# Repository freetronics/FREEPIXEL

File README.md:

Freetronics FreePixel Addressable RGB LED Module
=================================================
Copyright 2016 Freetronics Pty Ltd  
Freetronics site:  www.freetronics.com  
Freetronics email: info@freetronics.com  

This is an LED with a brain! Includes a bright RGB LED with a built-in
WS2812B constant-current, addressable, multi-channel LED driver. This
smart module can be daisy-chained, so you can connect a number of these
together in a string and drive each of the module colours individually
from your microcontroller.

Compatible with various Arduino libraries for the WS2812B, including
the FastLED library and the NeoPixel library.

Features:

 * Requires just 1 data connections.
 * Input and output headers on opposite sides of the board for easy
   daisy-chaining.

More information is available at:

  http://www.freetronics.com.au/freepixel

INSTALLATION
------------
The design is saved as an EAGLE project. EAGLE PCB design software is
available from www.cadsoftusa.com free for non-commercial use. To use
this project download it and place the directory containing these files
into the "eagle" directory on your computer.

DISTRIBUTION
------------
The specific terms of distribution of this project are governed by the
license referenced below.

LICENSE
-------
Licensed under the TAPR Open Hardware License (www.tapr.org/OHL).
The "license" folder within this repository also contains a copy of
this license in plain text format.

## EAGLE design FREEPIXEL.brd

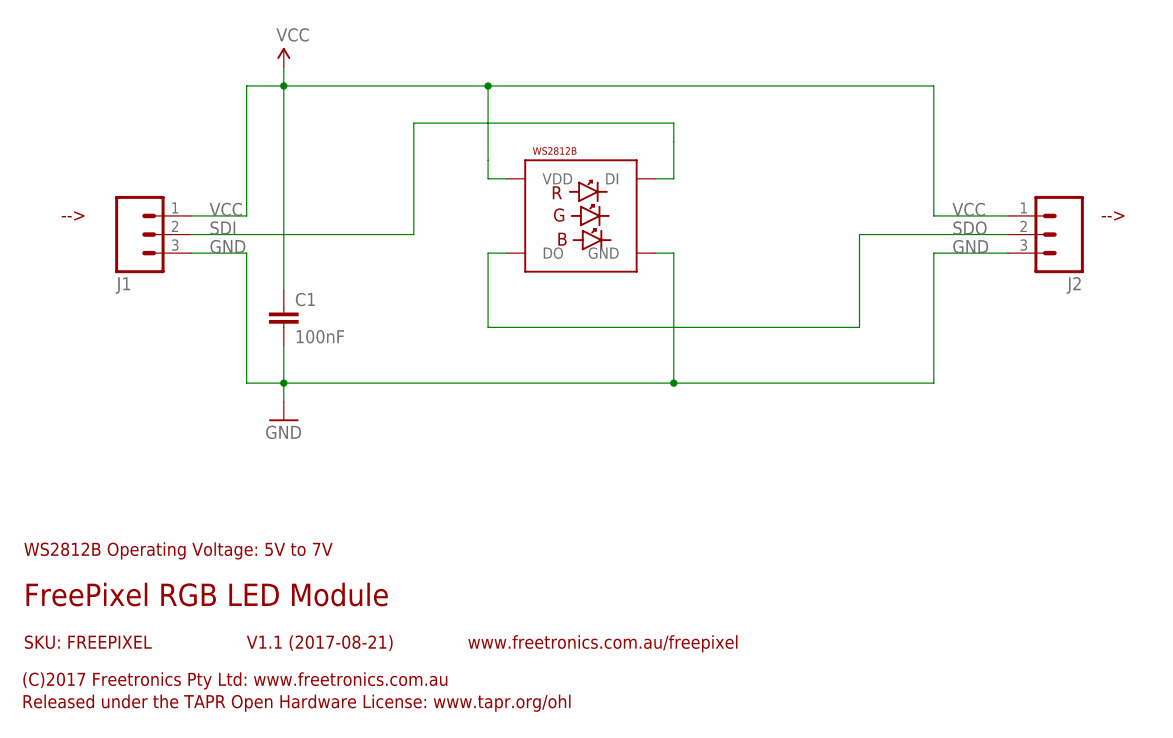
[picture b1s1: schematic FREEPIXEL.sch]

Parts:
C1: 100nF; 0603
J1, J2: M03PTH; 1X03
LED1: WS2812B5050; WS2812B

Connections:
GND: C1.2, J1.3, J2.3, LED1.3-GND (GND)
SDI: J1.2, LED1.4-DIN (DI)
SDO: J2.2, LED1.2-DOUT (DO)
VCC: C1.1, J1.1, J2.1, LED1.1-VDD (VDD)

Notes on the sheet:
FreePixel RGB LED Module
V1.1 (2017-08-21)
SKU: FREEPIXEL
(C)2017 Freetronics Pty Ltd: www.freetronics.com.au
Released under the TAPR Open Hardware License: www.tapr.org/ohl
www.freetronics.com.au/freepixel
WS2812B Operating Voltage: 5V to 7V
-->

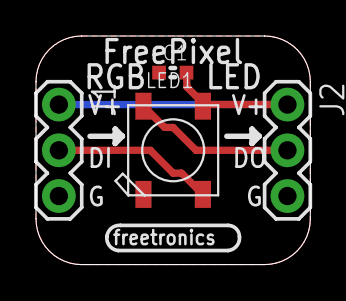
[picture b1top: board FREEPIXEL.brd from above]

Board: 2 copper layers, 15.2 x 12.7 mm, 4 parts (0 on the bottom side), 4 nets.

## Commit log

2016-03-07 Renamed files for beginning of conversion to WS2812B
2016-03-15 Redesigned using WS2812B integrated LED / controller
2016-03-30 Clarified schematic
2017-08-21 Fixed silkscreen label for DI (Data In) on bottom for v1.1 release
